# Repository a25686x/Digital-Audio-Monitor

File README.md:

monitor digital audio from SPDIF/AES3 and SDI video source

  CS8416:  select digital audio signals from AES and SDI with BNC and SFP connectors

  SSM3582A:  audio amplifier

  GS2971:  Digital audio demultiplex

  RS2228XN:  select SDI between SFP and BNC conncetor

  ESP8285:  system control

Using following software:

  Kicad 7.0 
  Fusion 360
  Arduino

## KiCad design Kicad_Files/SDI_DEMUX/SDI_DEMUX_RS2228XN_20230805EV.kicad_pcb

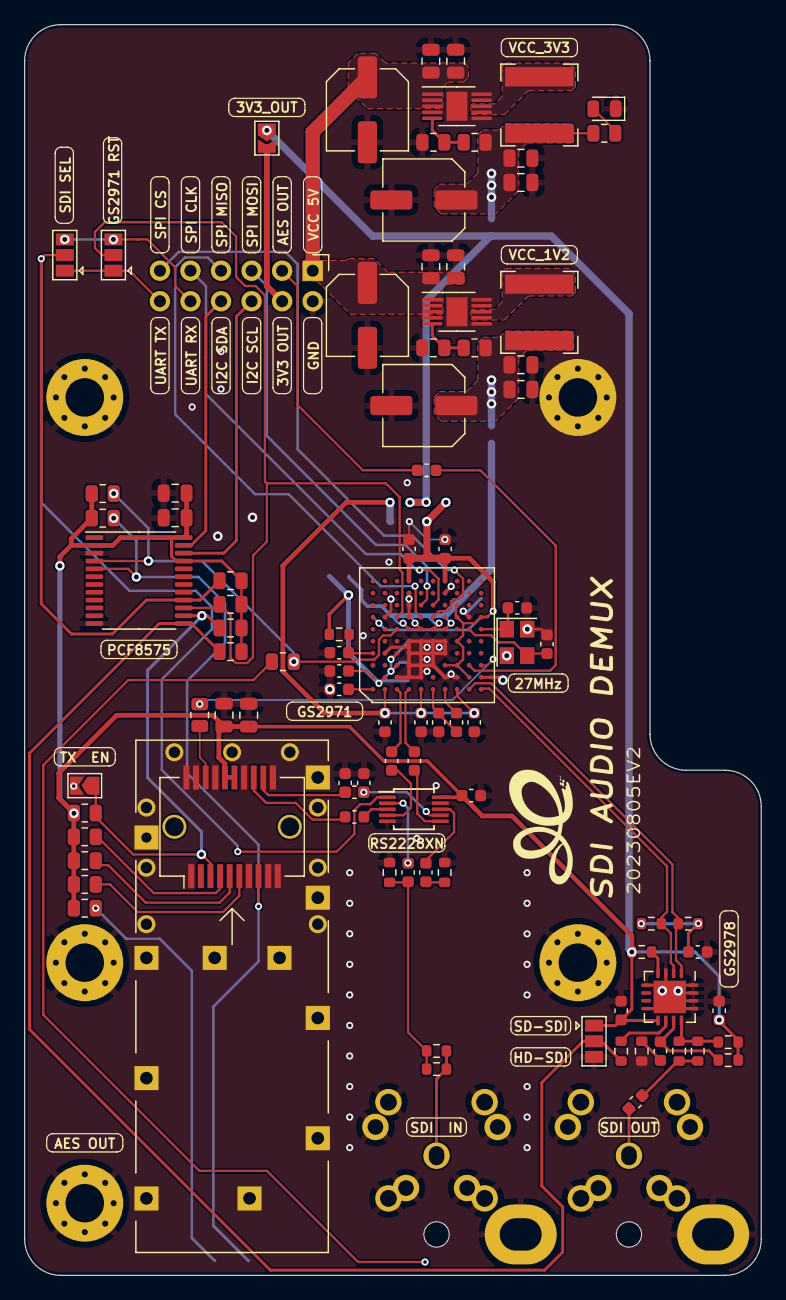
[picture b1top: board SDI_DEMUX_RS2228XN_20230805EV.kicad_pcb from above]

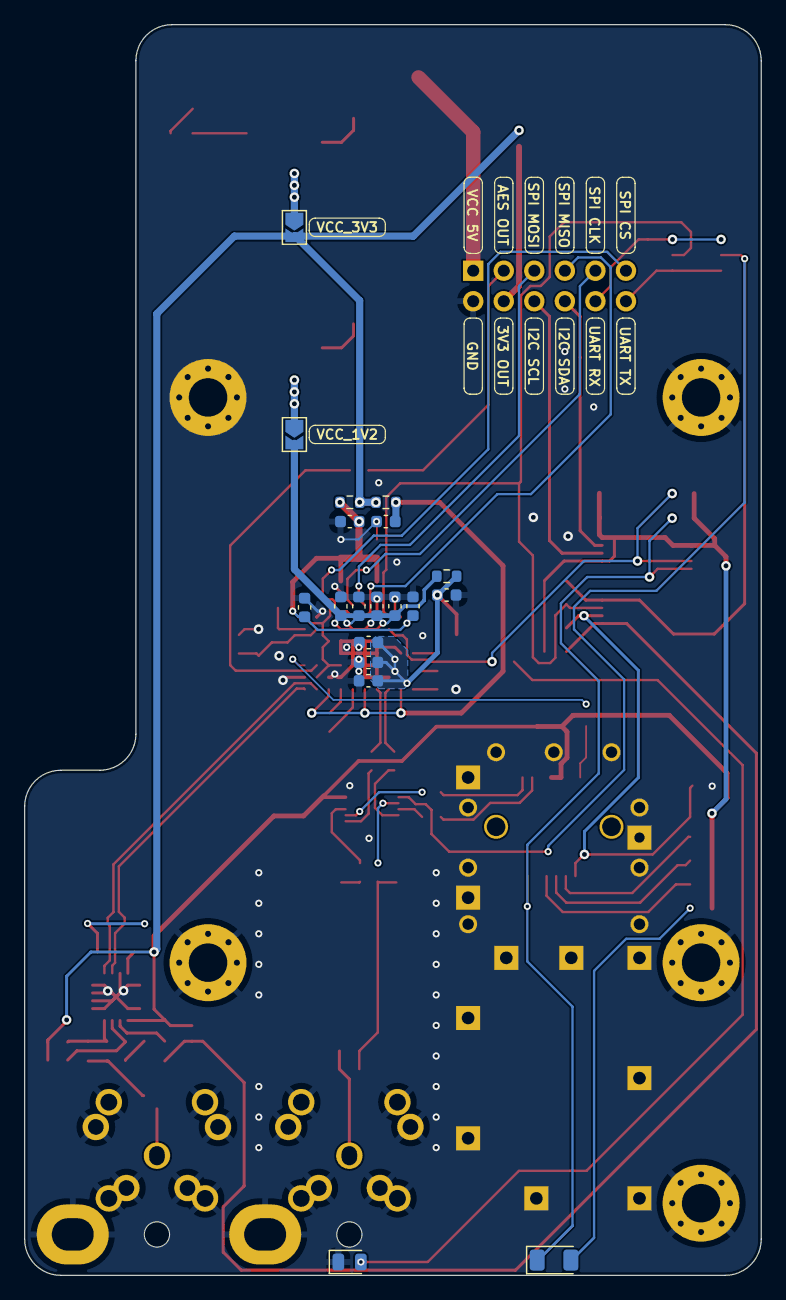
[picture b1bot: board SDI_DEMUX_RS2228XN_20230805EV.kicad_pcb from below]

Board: 2 copper layers, 61.2 x 104.0 mm, 118 parts (19 on the bottom side), 68 nets.

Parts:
C10, C26, C31, C42, C49, C51: 105; C_0603_1608Metric
C11, C12, C13, C14, C15, C16, C17, C27, C28, C29, C32, C33, C34, C35, C47, C48, C57: 10n; C_0603_1608Metric
C18: 226; C_0603_1608Metric
C41, C100, C101: 474; C_0603_1608Metric
C43, C44: 16p; C_0603_1608Metric
C50, C52: 475; C_0603_1608Metric
C105: 104; C_0603_1608Metric
C2701, C3302: 106; C_0805_2012Metric
C2702, C3102, C3202, C3301: 104; C_0805_2012Metric
C2711, C2712, C2721, C2722, C2723, C2724, C2731: 106; C_0603_1608Metric
C3101, C3106, C3201, C3206: 105; C_0805_2012Metric
C3103, C3104, C3203, C3204: 107; CP_Elec_6.3x7.7_20230725EV
C3105, C3205: 10n; C_0805_2012Metric
D102, D205: LED; LED_0805_2012Metric
D2701: Fiber RX OK(GREEN); LED_1206_3216Metric
J2701: SDI IN; Connector_SFP_and_Cage_UserEco1_20230723EV
J2702: SDI_OUT; BCJ-BPLHKA_TOP_UserEco1_20230722EV
J2705: SDI_IN; BCJ-BPLHKA_TOP_UserEco1_20230722EV
J3001: Conn_02x06_Odd_Even; PinHeader_2x06_P2.54mm_Vertical
JP1, JP3, JP2702: SolderJumper_3_Open; SolderJumper-3_P1.3mm_Open_Pad1.0x1.5mm
JP2, JP3001, JP3101, JP3201: SolderJumper_2_Open; SolderJumper-2_P1.3mm_Open_TrianglePad1.0x1.5mm
L3: 6.2n; R_0603_1608Metric
L4: 5.6n; R_0603_1608Metric
L3101, L3201: L; L_Bourns-SRN6028
MB3, MB4, MB5, MB6, MB7: MB; MountingHole_3.2mm_M3_Pad_Via_Eco1_20230801EV
R2, R10, R11, R50: 0R; R_0603_1608Metric
R3: 0R; R_0805_2012Metric
R7: 105R; R_0603_1608Metric
R40: 750R; R_0603_1608Metric
R41, R42, R43, R44, R45, R47: 75R; R_0603_1608Metric
R46: 37.4R; R_0603_1608Metric
R48, R49: 49.9; R_0603_1608Metric
R100, R205: 4.7k; R_0805_2012Metric
R2701, R2702, R2703, R2704: 4.7K; R_0805_2012Metric
R2705: 1K; R_0805_2012Metric
R3101: 450K; R_0805_2012Metric
R3102, R3201, R3202, R3301, R3302, R3303, R3304, R3311, R3312: 100K; R_0805_2012Metric
U1: GS2971; BGA-100_11.0x11.0mm_Layout10x10_P1.0mm_Ball0.5mm_Pad0.4mm_N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
U7: GS2978; QFN-16-1EP_4x4mm_P0.65mm_EP2.7x2.7mm
U2702: RS2228XN; MSOP-10_3x3mm_P0.5mm
U3101, U3201: AP2420; MSOP-10-1EP_3x3mm_P0.5mm_EP1.73x2.40mm_20230801EV
U3301: PCF8575PW; TSSOP-24_6.1x7.8mm_P0.65mm
Y1: 27M; Crystal_SMD_3225-4Pin_3.2x2.5mm

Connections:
/+1.2V: C14.1, C15.1, C16.1, C17.1, JP3201.2 (B), R10.2, U1.D6 (CORE_VDD), U1.E6 (CORE_VDD), U1.F6 (CORE_VDD), U1.G6 (CORE_VDD)
/+1.2VA: C26.1, C27.1, C28.1, C29.1, R7.2, R10.1, U1.B2 (PLL_VDD), U1.C3 (PLL_VDD), U1.C4 (PLL_VDD)
/+3.3VA: C10.1, C11.1, C12.1, C13.1, R2.1, U1.B1 (A_VDD), U1.E1 (SDI_VDD), U1.H1 (BUF_VDD)
/AES_SFP_TX+: J2701.18 (TD+), R3.1
/AOUT_1/2: C105.2, J3001.4
/AOUT_3/4: R3.2, U1.K3 (AOUT_3/4)
/GS2971_IN+: C2711.2, U1.C1 (SDI+)
/GS2971_IN-: C2712.2, U1.D1 (SDI-)
/GS2971_RST: JP1.2 (C), R3303.1, U1.C7 (RESET-), U3301.15 (P12)
/GS2971_STAT5: R205.2, R3311.2, U1.C6 (STAT5), U3301.4 (P00)
/IO_VDD: C31.1, C32.1, C33.1, C34.1, C35.1, R11.1, U1.A7 (IO_VDD), U1.D10 (IO_VDD), U1.G3 (RC_BYP), U1.G10 (IO_VDD), U1.H3 (AUDIO_EN/DIS), U1.H5 (TIM_861), U1.H7 (20BIT_10BIT), U1.H8 (IOPROC_EN/DIS), U1.J2 (SDO_EN/DIS), U1.K7 (IO_VDD)
/MCU_3V3_OUT: J3001.3, JP3001.2 (B)
/MCU_I2C_SCL: J3001.5, U3301.22 (SCL)
/MCU_I2C_SDA: J3001.7, U3301.23 (SDA)
/MCU_SPI_CLK: J3001.10, U1.F8 (SCLK_TCK)
/MCU_SPI_CS: J3001.12, U1.F7 (CS_TMS)
/MCU_SPI_MISO: J3001.8, U1.E7 (SDOUT_TDO)
/MCU_SPI_MOSI: J3001.6, U1.E8 (SDIN_TDI)
/MCU_UART_RX: J3001.9, JP1.3 (B), JP2702.3 (B)
/MCU_UART_TX: J3001.11, JP1.1 (A), JP2702.1 (A)
/SDI_IN+: C49.2, U2702.2 (HSD0_P)
/SDI_IN-: C51.2, U2702.8 (HSD0_M)
/SDI_INPUT_SELECT: JP2702.2 (C), R3304.1, U2702.1 (SEL), U3301.16 (P13)
/SDO+: R49.1, U1.J1 (SDO+), U7.1 (SDI+)
/SDO-: R48.1, U1.K1 (SDO-), U7.2 (SDI-)
/SD_HD_SLEW: JP3.2 (C), R50.2, R3301.1, U3301.13 (P10)
/SFP_RD+: C2721.1, J2701.13 (RD+)
/SFP_RD-: C2722.1, C2723.2, J2701.12 (RD-)
/SFP_RX_LOSS: D2701.1 (K), J2701.8 (RX_LOS), R3312.2, U3301.5 (P01)
/SFP_TX_DISABLE: J2701.3 (TX_DISABLE), JP2.1 (A), R2704.2, R3302.1, U3301.14 (P11)
/VCC5V_IN: C3101.1, C3102.1, C3103.1, C3201.1, C3202.1, C3203.1, J3001.2, U3101.1 (EN), U3101.2 (VDD), U3101.3 (PVDD), U3201.1 (EN), U3201.2 (VDD), U3201.3 (PVDD)
/VCC_3.3V: C47.1, C48.1, C2701.1, C2702.1, C2731.1, C3301.1, C3302.1, J2701.15 (VccR), J2701.16 (VccT), JP3.1 (A), JP3001.1 (A), JP3101.2 (B), R2.2, R11.2, R40.1, R41.1, R43.1, R2701.1, R2702.1, R2703.1, R2704.1, R2705.2, R3301.2, R3302.2, R3303.2, R3304.2, R3311.1, R3312.1, U7.9 (VCC), U2702.10 (VCC), U3301.2 (A1), U3301.21 (A0), U3301.24 (VCC)
GNDD: C10.2, C11.2, C12.2, C13.2, C14.2, C15.2, C16.2, C17.2, C18.2, C26.2, C27.2, C28.2, C29.2, C31.2, C32.2, C33.2, C34.2, C35.2, C41.1, C42.1, C43.2, C44.1, C47.2, C48.2, C57.2, C101.1, C2701.2, C2702.2, C2723.1, C2724.1, C2731.2, C3101.2, C3102.2, C3103.2, C3104.2, C3105.2, C3106.2, C3201.2, C3202.2, C3203.2, C3204.2, C3205.2, C3206.2, C3301.2, C3302.2, D102.1 (K), D205.1 (K), J2701.1 (VeeT), J2701.7 (RS0), J2701.9 (RS1), J2701.10 (VeeR), J2701.11 (VeeR), J2701.14 (VeeR), J2701.17 (VeeT), J2701.19 (TD-), J2701.20 (VeeT), J2701.CAGE, J2702.2 (Ext), J2705.2 (Ext), J3001.1, JP2.2 (B), JP3.3 (B), MB3.1, MB4.1, MB5.1, MB6.1, MB7.1, R44.1, R45.2, R46.2, R3102.2, R3202.2, U1.B4 (VCO_GND), U1.B7 (IO_GND), U1.C2 (A_GND), U1.D2 (A_GND), U1.D3 (A_GND), U1.D4 (PLL_GND), U1.D5 (CORE_GND), U1.D7 (SW_EN), U1.D8 (JTAG/HOST), U1.D9 (IO_GND), U1.E2 (SDI_GND), U1.E3 (A_GND), U1.E4 (PLL_GND), U1.E5 (CORE_GND), U1.F3 (A_GND), U1.F4 (PLL_GND), U1.F5 (CORE_GND), U1.G2 (A_GND), U1.G4 (CORE_GND), U1.G5 (CORE_GND), U1.G9 (IO_GND), U1.H2 (BUF_GND), U1.J7 (IO_GND), U1.K2 (STANDBY), U7.3 (GND), U7.5 (NC), U7.8 (NC), U7.13 (NC), U7.14 (NC), U7.15 (NC), U7.16 (NC), U7.17 (TAB), U2702.5 (GND), U2702.9 (nOE), U3101.4 (GND), U3101.6 (GND), U3101.9 (PGND), U3101.10 (PGND), U3101.11 (GND), U3201.4 (GND), U3201.6 (GND), U3201.9 (PGND), U3201.10 (PGND), U3201.11 (GND), U3301.3 (A2), U3301.12 (GND), Y1.2, Y1.4
unnamed: C49.1, L3.2, R42.1, R45.1
unnamed: C50.2, R44.2
unnamed: C51.1, R46.1
unnamed: C52.1, L4.2, R47.1
unnamed: C57.1, R48.2, R49.2
unnamed: D102.2 (A), R100.2
unnamed: D205.2 (A), R205.1
unnamed: D2701.2 (A), R2705.1
unnamed: J2701.6 (MOD_ABS), R2703.2
unnamed: J2701.5 (SCL), R2702.2
unnamed: J2701.4 (SDA), R2701.2
unnamed: C52.2, J2702.1 (In)
unnamed: J2705.1 (In), L3.1, R42.2
unnamed: C3104.1, C3105.1, C3106.1, JP3101.1 (A), L3101.2, R100.1, R3101.1
unnamed: C3204.1, C3205.1, C3206.1, JP3201.1 (A), L3201.2, R3201.1
unnamed: L3101.1, U3101.7 (LX), U3101.8 (LX)
unnamed: L3201.1, U3201.7 (LX), U3201.8 (LX)
unnamed: C100.1, C101.2, U1.F1 (AGC+)
unnamed: C100.2, U1.G1 (AGC-)
unnamed: C105.1, U1.J3 (AOUT_1/2)
unnamed: C41.2, U1.A2 (LF)
unnamed: C42.2, U1.A1 (VBG)
unnamed: C18.1, R7.1, U1.A4 (VCO_VDD)
unnamed: C44.2, U1.K6 (XTAL1), Y1.1
unnamed: C43.1, U1.J6 (XTAL2), Y1.3
unnamed: R40.2, U7.4 (RSET)
unnamed: L4.1, R41.2, R47.2, U7.12 (SDO+)
unnamed: C50.1, R43.2, U7.11 (SDO-)
unnamed: R50.1, U7.10 (SD/HD)
unnamed: C2712.1, U2702.6 (D_N)
unnamed: C2711.1, U2702.4 (D_P)
unnamed: C2722.2, C2724.2, U2702.7 (HSD1_M)
unnamed: C2721.2, U2702.3 (HSD1_P)
unnamed: R3101.2, R3102.1, U3101.5 (FB)
unnamed: R3201.2, R3202.1, U3201.5 (FB)

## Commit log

2023-08-22 Create MCU
2023-08-22 Create 3D print step files
